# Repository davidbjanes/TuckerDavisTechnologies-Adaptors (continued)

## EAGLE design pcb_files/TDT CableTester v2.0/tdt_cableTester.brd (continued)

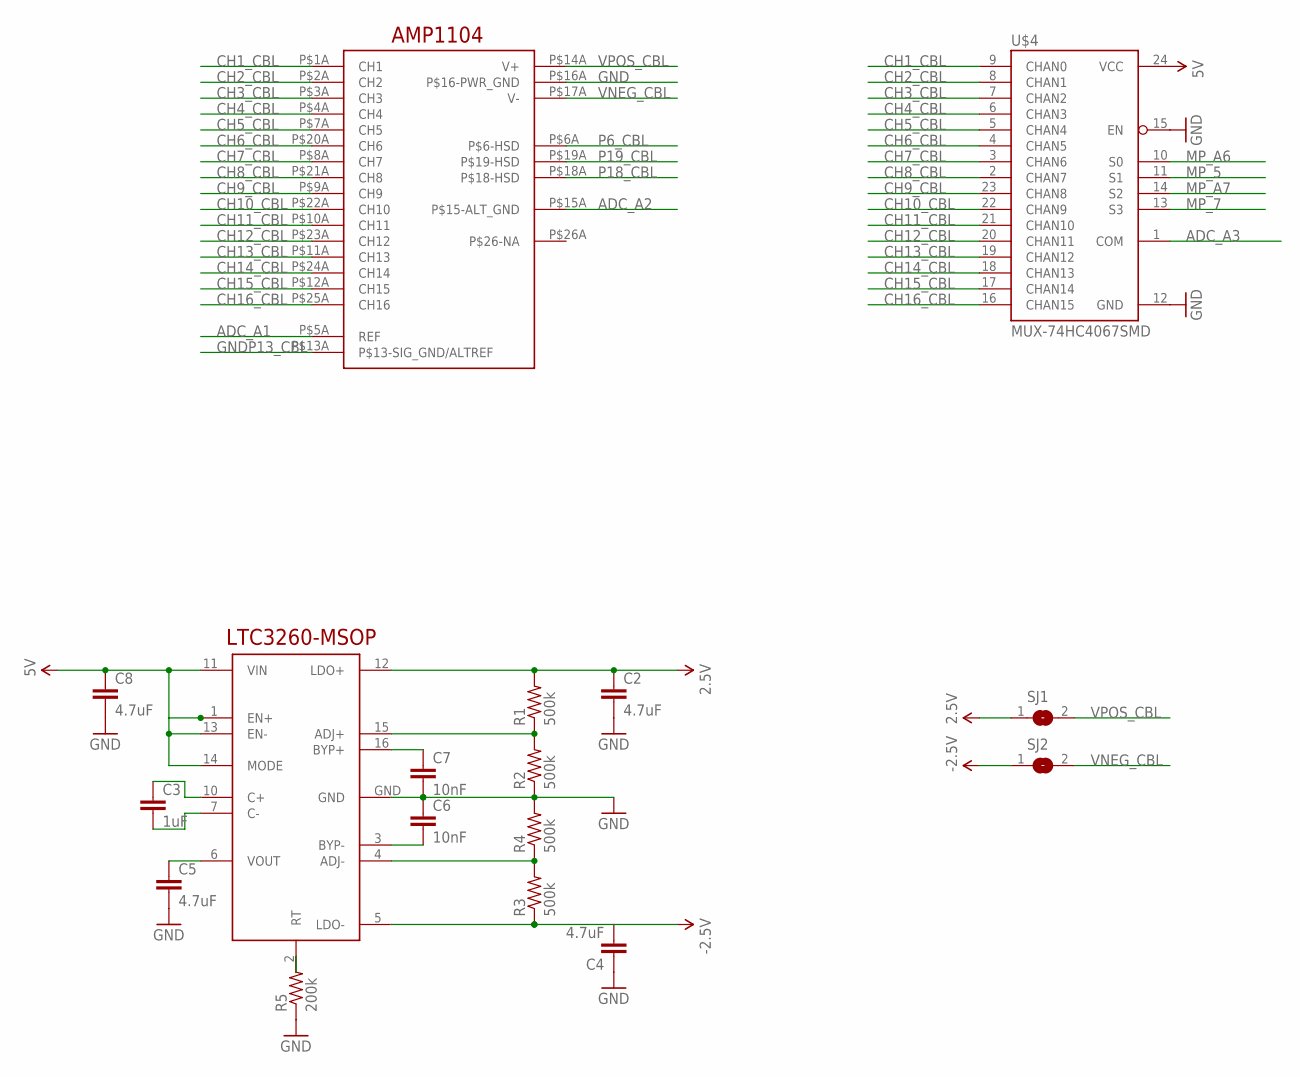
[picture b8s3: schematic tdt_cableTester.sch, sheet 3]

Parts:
C2, C4, C5, C8: 4.7uF; 0805
C3: 1uF; 0805
C6, C7: 10nF; 0805
R1, R2, R3, R4: 500k; 0805
R5: 200k; 0805
SJ1, SJ2: SJ
U$3: AMP1104
U$4: MUX-74HC4067SMD; SSOP24
U$7: LTC3260-MSOP; MSOP16

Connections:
2.5V: C2.1, R1.2, SJ1.1, U$7.12 (LDO+)
5V: C8.1, U$4.24 (VCC), U$7.1 (EN+), U$7.11 (VIN), U$7.13 (EN-), U$7.14 (MODE); also elsewhere on the board
-2.5V: C4.2, R3.1, SJ2.1, U$7.5 (LDO-)
ADC_A1: U$3.P$5A (REF); also elsewhere on the board
ADC_A2: U$3.P$15A (P$15-ALT_GND); also elsewhere on the board
ADC_A3: U$4.1 (COM); also elsewhere on the board
CH1_CBL: U$3.P$1A (CH1), U$4.9 (CHAN0)
CH2_CBL: U$3.P$2A (CH2), U$4.8 (CHAN1)
CH3_CBL: U$3.P$3A (CH3), U$4.7 (CHAN2)
CH4_CBL: U$3.P$4A (CH4), U$4.6 (CHAN3)
CH5_CBL: U$3.P$7A (CH5), U$4.5 (CHAN4)
CH6_CBL: U$3.P$20A (CH6), U$4.4 (CHAN5)
CH7_CBL: U$3.P$8A (CH7), U$4.3 (CHAN6)
CH8_CBL: U$3.P$21A (CH8), U$4.2 (CHAN7)
CH9_CBL: U$3.P$9A (CH9), U$4.23 (CHAN8)
CH10_CBL: U$3.P$22A (CH10), U$4.22 (CHAN9)
CH11_CBL: U$3.P$10A (CH11), U$4.21 (CHAN10)
CH12_CBL: U$3.P$23A (CH12), U$4.20 (CHAN11)
CH13_CBL: U$3.P$11A (CH13), U$4.19 (CHAN12)
CH14_CBL: U$3.P$24A (CH14), U$4.18 (CHAN13)
CH15_CBL: U$3.P$12A (CH15), U$4.17 (CHAN14)
CH16_CBL: U$3.P$25A (CH16), U$4.16 (CHAN15)
GND: C2.2, C4.1, C5.2, C6.1, C7.2, C8.2, R2.1, R4.2, R5.1, U$3.P$16A (P$16-PWR_GND), U$4.12 (GND), U$4.15 (EN), U$7.GND; also elsewhere on the board
GNDP13_CBL: U$3.P$13A (P$13-SIG_GND/ALTREF)
MP_5: U$4.11 (S1); also elsewhere on the board
MP_7: U$4.13 (S3); also elsewhere on the board
MP_A6: U$4.10 (S0); also elsewhere on the board
MP_A7: U$4.14 (S2); also elsewhere on the board
unnamed: R1.1, R2.2, U$7.15 (ADJ+)
unnamed: C6.2, U$7.3 (BYP-)
unnamed: R5.2, U$7.2 (RT)
unnamed: C7.1, U$7.16 (BYP+)
unnamed: R3.2, R4.1, U$7.4 (ADJ-)
unnamed: C3.1, U$7.10 (C+)
unnamed: C3.2, U$7.7 (C-)
unnamed: C5.1, U$7.6 (VOUT)
P6_CBL: U$3.P$6A (P$6-HSD)
P18_CBL: U$3.P$18A (P$18-HSD)
P19_CBL: U$3.P$19A (P$19-HSD)
VNEG_CBL: SJ2.2, U$3.P$17A (V-)
VPOS_CBL: SJ1.2, U$3.P$14A (V+)

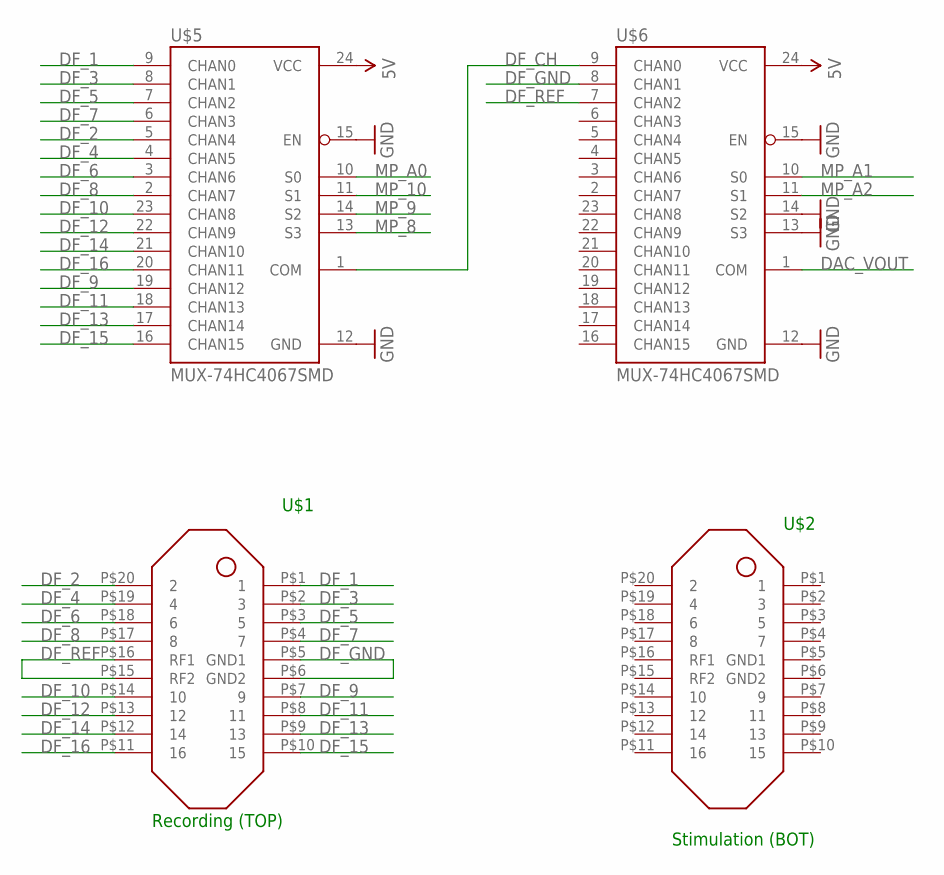
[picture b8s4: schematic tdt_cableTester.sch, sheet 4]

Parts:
U$1, U$2: DF30_HEADER; DF30FC-20DP-0.4V
U$5, U$6: MUX-74HC4067SMD; SSOP24

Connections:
5V: U$5.24 (VCC), U$6.24 (VCC); also elsewhere on the board
DAC_VOUT: U$6.1 (COM); also elsewhere on the board
DF_1: U$1.P$1 (1), U$5.9 (CHAN0)
DF_2: U$1.P$20 (2), U$5.5 (CHAN4)
DF_3: U$1.P$2 (3), U$5.8 (CHAN1)
DF_4: U$1.P$19 (4), U$5.4 (CHAN5)
DF_5: U$1.P$3 (5), U$5.7 (CHAN2)
DF_6: U$1.P$18 (6), U$5.3 (CHAN6)
DF_7: U$1.P$4 (7), U$5.6 (CHAN3)
DF_8: U$1.P$17 (8), U$5.2 (CHAN7)
DF_9: U$1.P$7 (9), U$5.19 (CHAN12)
DF_10: U$1.P$14 (10), U$5.23 (CHAN8)
DF_11: U$1.P$8 (11), U$5.18 (CHAN13)
DF_12: U$1.P$13 (12), U$5.22 (CHAN9)
DF_13: U$1.P$9 (13), U$5.17 (CHAN14)
DF_14: U$1.P$12 (14), U$5.21 (CHAN10)
DF_15: U$1.P$10 (15), U$5.16 (CHAN15)
DF_16: U$1.P$11 (16), U$5.20 (CHAN11)
DF_CH: U$5.1 (COM), U$6.9 (CHAN0)
DF_GND: U$1.P$5 (GND1), U$1.P$6 (GND2), U$6.8 (CHAN1)
DF_REF: U$1.P$15 (RF2), U$1.P$16 (RF1), U$6.7 (CHAN2)
GND: U$5.12 (GND), U$5.15 (EN), U$6.12 (GND), U$6.13 (S3), U$6.14 (S2), U$6.15 (EN); also elsewhere on the board
MP_8: U$5.13 (S3); also elsewhere on the board
MP_9: U$5.14 (S2); also elsewhere on the board
MP_10: U$5.11 (S1); also elsewhere on the board
MP_A0: U$5.10 (S0); also elsewhere on the board
MP_A1: U$6.10 (S0); also elsewhere on the board
MP_A2: U$6.11 (S1); also elsewhere on the board

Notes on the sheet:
U$2
U$1
Recording (TOP)
Stimulation (BOT)

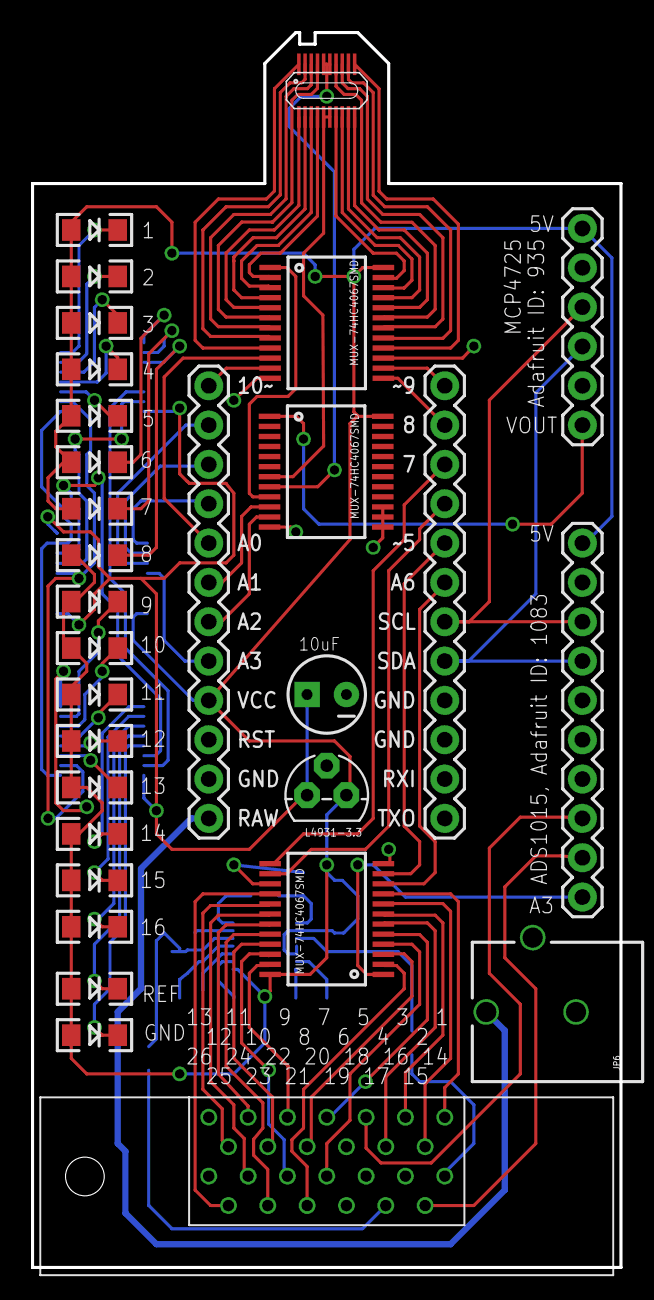
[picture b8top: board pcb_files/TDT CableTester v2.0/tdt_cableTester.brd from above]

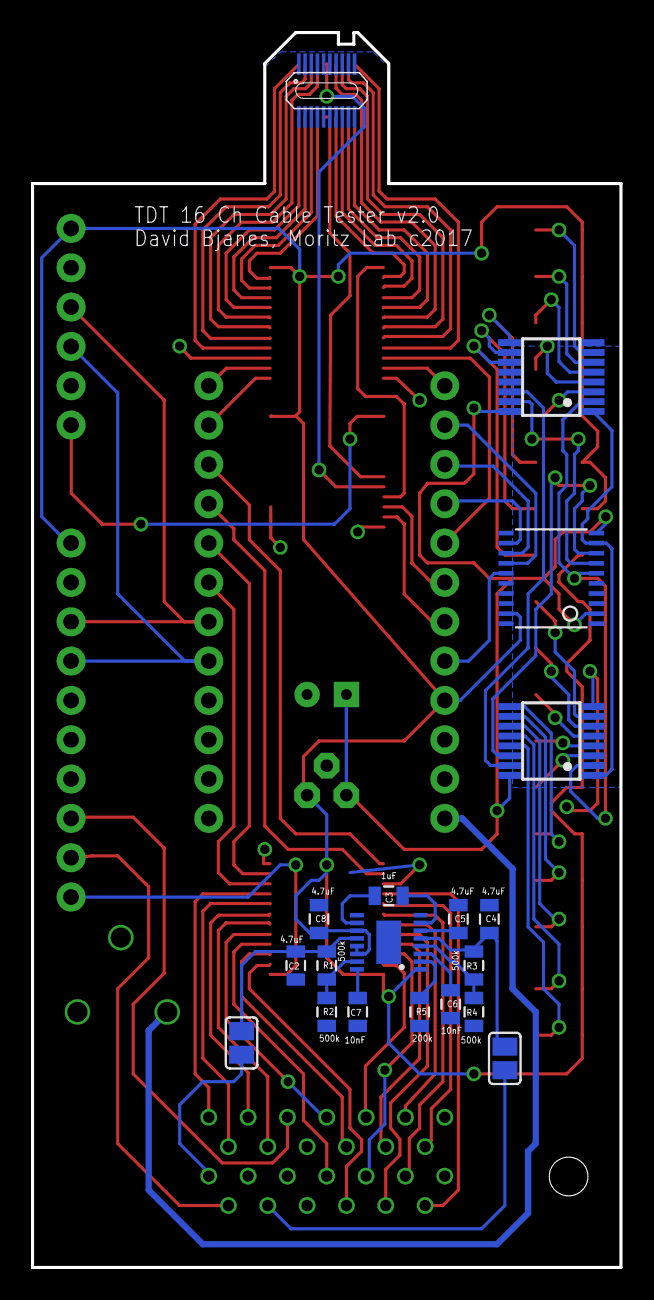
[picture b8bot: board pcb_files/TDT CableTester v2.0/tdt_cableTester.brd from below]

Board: 2 copper layers, 38.0 x 79.8 mm, 49 parts (19 on the bottom side), 94 nets.

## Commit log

2019-02-26 add microcontroller code
2019-02-26 added .gitignore
2019-02-26 added various pcb boards and versions. Folders labeled "ORDERED" means board has been created and debugged.
